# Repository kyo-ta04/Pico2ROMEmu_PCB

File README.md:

# Pico2ROMEmu\_PCB

Pico2ROMEmu PCB
This is a KiCad project for a Pico2ROMEmu ROM emulator.  
For more information, please see [Pico2ROMEmu](https://github.com/kyo-ta04/Pico2ROMEmuBR).  
- KiCad Version: 9.0.5  
- License: MIT  
- Includes: Schematic, PCB layout, BOM, Gerber files  

KiCanvas view ->
[schematics](https://kicanvas.org/?github=https%3A%2F%2Fgithub.com%2Fkyo-ta04%2FPico2ROMEmu_PCB%2Fblob%2Fmaster%2FPico2ROMEmu_PCB.kicad_sch), 
[board](https://kicanvas.org/?github=https%3A%2F%2Fgithub.com%2Fkyo-ta04%2FPico2ROMEmu_PCB%2Fblob%2Fmaster%2FPico2ROMEmu_PCB.kicad_pcb)  

Gerber file -> [Pico2ROMEmu_PCB_0.1.zip](https://github.com/kyo-ta04/Pico2ROMEmu_PCB/blob/master/production/Pico2ROMEmu_PCB_0.1.zip)

## Schematics and Documents
- Assembly instructions (note.com)
  - [Pico2ROMEmuの組み立て方](https://note.com/quiet_duck4046/n/n425d6b7e8d55?sub_rt=share_sb)
  - [Super AKI-80の組み立て方(最少部品編)](https://note.com/quiet_duck4046/n/n32906e1dfb96?sub_rt=share_sb)  
- 
- 

## Disclaimer
This software is provided as is. The author is not responsible for any damage.

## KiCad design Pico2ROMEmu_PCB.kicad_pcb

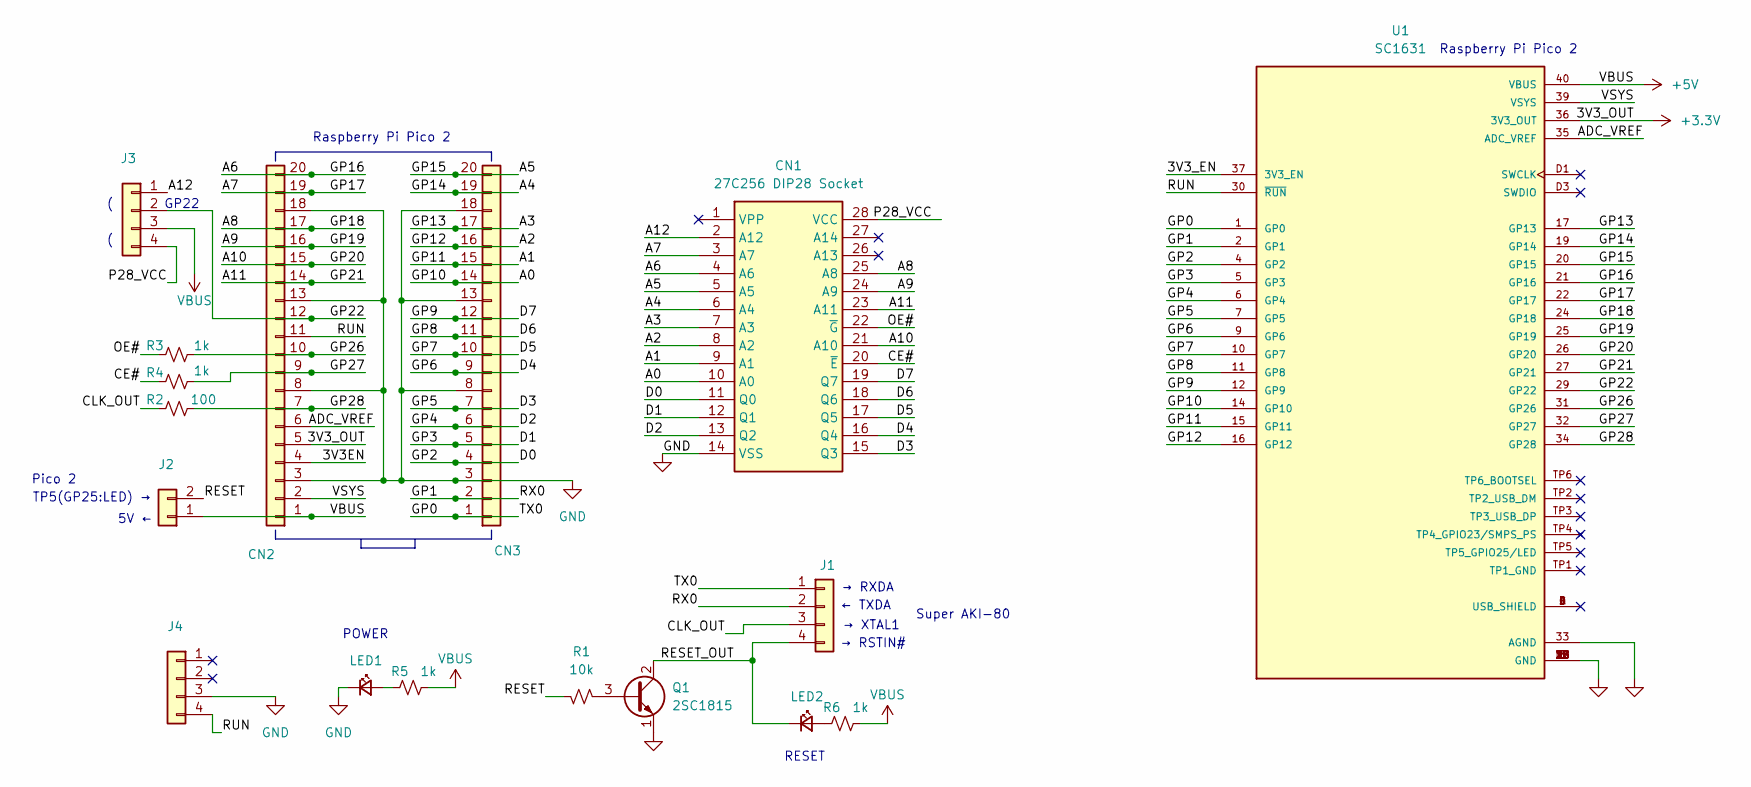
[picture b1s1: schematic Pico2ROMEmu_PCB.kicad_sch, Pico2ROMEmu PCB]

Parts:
CN1: 27C256 DIP28 Socket; DIP-28_W15.24mm_Socket; Manufacturer_Part_Number M27C256B-15F1; Mouser Part Number 511-M27C256B-15F
CN2, CN3: Conn_01x20; PinSocket_1x20_P2.54mm_Vertical
J1, J3: Conn_01x04; PinHeader_1x04_P2.54mm_Horizontal
J2: Conn_01x02; PinHeader_1x02_P2.54mm_Vertical
J4: Conn_01x04; PinHeader_1x04_P2.54mm_Vertical
LED1: LED_Small; LED_D3.0mm
LED2: LED_Small; LED_D3.0mm_Clear
Q1: 2SC1815; TO-92_Inline
R1: 10k; R_Axial_DIN0204_L3.6mm_D1.6mm_P5.08mm_Horizontal
R2: 100; R_Axial_DIN0204_L3.6mm_D1.6mm_P5.08mm_Horizontal
R3, R4, R5, R6: 1k; R_Axial_DIN0204_L3.6mm_D1.6mm_P5.08mm_Horizontal
U1: SC1631; MODULE_SC0915; PARTREV 1.9

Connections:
+3.3V: CN2.5, U1.36 (3V3_OUT)
+5V: CN2.1, J2.1, J3.3, R5.1, R6.1, U1.40 (VBUS)
/3V3EN: CN2.4
/A0: CN1.10 (A0), CN3.14, U1.14 (GP10)
/A1: CN1.9 (A1), CN3.15, U1.15 (GP11)
/A2: CN1.8 (A2), CN3.16, U1.16 (GP12)
/A3: CN1.7 (A3), CN3.17, U1.17 (GP13)
/A4: CN1.6 (A4), CN3.19, U1.19 (GP14)
/A5: CN1.5 (A5), CN3.20, U1.20 (GP15)
/A6: CN1.4 (A6), CN2.20, U1.21 (GP16)
/A7: CN1.3 (A7), CN2.19, U1.22 (GP17)
/A8: CN1.25 (A8), CN2.17, U1.24 (GP18)
/A9: CN1.24 (A9), CN2.16, U1.25 (GP19)
/A10: CN1.21 (A10), CN2.15, U1.26 (GP20)
/A11: CN1.23 (A11), CN2.14, U1.27 (GP21)
/A12: CN1.2 (A12), J3.1
/ADC_VREF: CN2.6, U1.35 (ADC_VREF)
/CE#: CN1.20 (~E), R4.2
/CLK_OUT: J1.3, R2.2
/D0: CN1.11 (Q0), CN3.4, U1.4 (GP2)
/D1: CN1.12 (Q1), CN3.5, U1.5 (GP3)
/D2: CN1.13 (Q2), CN3.6, U1.6 (GP4)
/D3: CN1.15 (Q3), CN3.7, U1.7 (GP5)
/D4: CN1.16 (Q4), CN3.9, U1.9 (GP6)
/D5: CN1.17 (Q5), CN3.10, U1.10 (GP7)
/D6: CN1.18 (Q6), CN3.11, U1.11 (GP8)
/D7: CN1.19 (Q7), CN3.12, U1.12 (GP9)
/GP0: CN3.1, J1.1, U1.1 (GP0)
/GP1: CN3.2, J1.2, U1.2 (GP1)
/GP22: CN2.12, J3.2, U1.29 (GP22)
/GP26: CN2.10, R3.1, U1.31 (GP26)
/GP27: CN2.9, R4.1, U1.32 (GP27)
/GP28: CN2.7, R2.1, U1.34 (GP28)
/OE#: CN1.22 (~G), R3.2
/P28_VCC: CN1.28 (VCC), J3.4
/RESET: J2.2, R1.1
/RESET_OUT: J1.4, LED2.1 (K), Q1.2 (C)
/RUN: CN2.11, J4.4, U1.30 (~RUN)
/VSYS: CN2.2, U1.39 (VSYS)
GND: CN1.14 (VSS), CN2.3, CN2.8, CN2.13, CN2.18, CN3.3, CN3.8, CN3.13, CN3.18, J4.3, LED1.1 (K), Q1.1 (E), U1.3 (GND), U1.8 (GND), U1.13 (GND), U1.18 (GND), U1.23 (GND), U1.28 (GND), U1.33 (AGND), U1.38 (GND), U1.D2 (GND)
unnamed: LED1.2 (A), R5.2
unnamed: LED2.2 (A), R6.2
unnamed: Q1.3 (B), R1.2
unnamed: U1.A (USB_SHIELD), U1.B (USB_SHIELD), U1.C (USB_SHIELD), U1.D (USB_SHIELD)

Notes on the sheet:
← TXDA
→ RXDA
RESET
TP5(GP25:LED) →
→ XTAL1
Pico 2
POWER
5V ←
Super AKI-80
GP22
Raspberry Pi Pico 2
→ RSTIN#

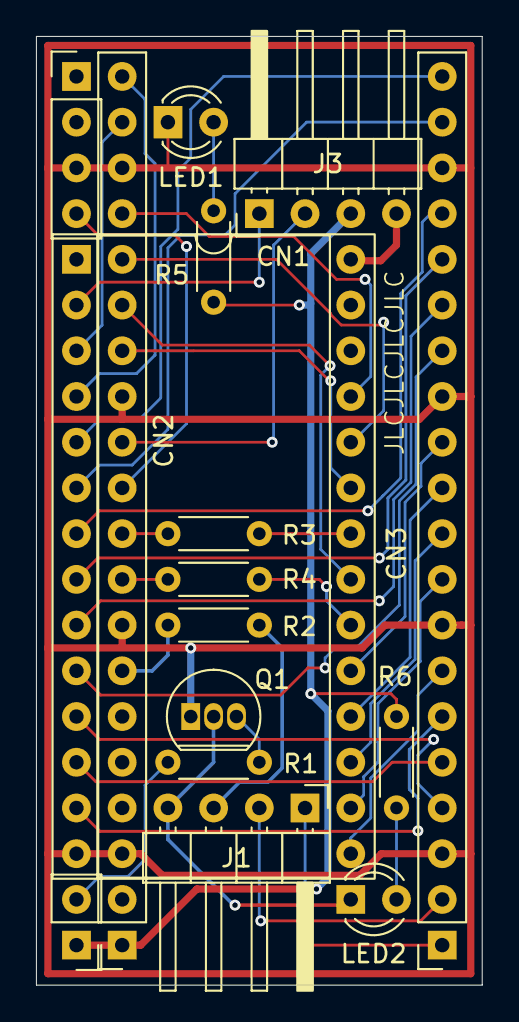
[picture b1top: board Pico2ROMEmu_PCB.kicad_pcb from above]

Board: 2 copper layers, 24.8 x 52.7 mm, 16 parts (0 on the bottom side), 39 nets.

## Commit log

2025-10-16 init
2025-10-16 add KiCanvas view
2025-10-16 change img file
2025-10-16 change img
2025-10-16 Modify the .gitignore file
2025-10-16 Modify
2025-10-24 modifi README
